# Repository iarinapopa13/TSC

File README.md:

# TSC
### Iarina-Ioana Popa, 332CA

# OpenBook eBook Reader – Hardware Overview
Acest proiect de eBook Reader utilizeaza microcontrollerul *ESP32-C6*, fiind proiectat pentru consum redus de energie, conectivitate avansata si adaptabilitate hardware.

## Diagrama Block

## Microcontroller – ESP32-C6
- *Arhitectura:* RISC-V 32-bit
- *Conectivitate:* WiFi 6, Bluetooth 5.0 LE
- *Interfete disponibile:* SPI, I2C, UART, PWM, GPIO
- *Eficienta energetica:* moduri deep sleep implementate

## Display E-Paper
- *Conectivitate:* Header de 20 pini dedicat
- *Protocol:* SPI + GPIO
 - Semnale principale: EPD_CS, EPD_DC, EPD_RST, EPD_BUSY, etc.
- *Beneficii:* zero consum in stare inactiva, vizibilitate superioara la lumina naturala

## Ceas Timp Real – DS3231SN
- *Caracteristici:* Precizie ridicata (±2 ppm)
- *Protocol:* I2C (partajat pe SDA/SCL)
- *Alimentare secundara:* Supercapacitor

## Senzor Ambiental – BME688
- *Masuratori:* Temperatura, Umiditate, Presiune atmosferica, VOCs
- *Interfata:* I2C
 - SDA: IO1
 - SCL: IO2
- *Alimentare:* 3.3V
- *Adresa I2C:* 0x76

## Sistem de Alimentare
### MAX17048 – Monitor Baterie
- *Rol:* Masurare capacitate baterie LiPo
- *Protocol:* I2C (IO1, IO2)
### MCP73831 – Controller Incarcare
- *Functionalitate:* Incarcare baterie LiPo (USB la 3.7V)
- *Capacitate:* ~500 mA
- *Indicator:* LED status incarcare
### XC6204 – Regulator LDO
- *Tensiune intrare:* 5V (USB)
- *Tensiune iesire:* 3.3V
- *Capacitate curent:* 200 mA
- *Eficienta energetica:* < 1 µA in standby

## Memorie si Stocare
### Card microSD
- *Protocol:* SPI (IO4–IO9)
- *Utilizare:* Stocare eBooks, setari
### Memorie Flash – W25Q512JV (64MB)
- *Protocol:* SPI (pini dedicati: IO20–IO23)
- *Utilizare:* Stocare firmware, fonturi, resurse

## Supervisor Tensiune & Resetare
- *Component:* BD52xx
- *Rol:* Monitorizare tensiune si resetare sigura
- *Pin control:* IO0

## Extensie I2C – Qwiic / Stemma QT
- *Conector:* 4 pini (3V3, GND, SDA, SCL)
- *Protocol:* I2C (IO1, IO2)
- *Ecosistem:* Compatibil cu module Adafruit / SparkFun

## Profil Consum Energetic
| Componenta             | Mod Activ       | Mod Standby    |
|------------------------|-----------------|----------------|
| ESP32-C6               | 80–150 mA       | <10 µA         |
| E-Paper                | 20–30 mA        | 0 µA           |
| BME688                 | 1.1 mA          | 0.15 µA        |
| RTC DS3231SN           | 200 µA          | 2 µA           |
| SD Card                | 20–100 mA       | 0.2 µA         |
| MAX17048               | 50 µA           | 1 µA           |
| NOR Flash              | 20 mA           | 5 µA           |

## Mapare Pini – ESP32-C6
| Functionalitate        | Pini GPIO            |
|------------------------|----------------------|
| Card SD (SPI)          | IO4, IO5, IO6, IO9   |
| Display E-Paper        | IO10–IO19            |
| I2C (RTC, Senzor)      | IO1 (SDA), IO2 (SCL) |
| Flash SPI extern       | IO20–IO23            |
| Buton Reset / Boot     | IO0                  |

## BOM (Bill Of Materials)
| Componenta | Link Cumpărare | Datasheet |
|------------|-----------------|-----------|
| Condensatoare Tantalum | [Buy](https://ro.mouser.com/ProductDetail/KYOCERA-AVX/TAJW107M010RNJ?qs=Wtp%252Bf%2FAeVqIH8v1VxV%252B1Rg%3D%3D) | [Datasheet](https://ro.mouser.com/datasheet/2/40/TAJ-3165264.pdf) |
| Rezistente R0402 | [Buy](https://store.comet.srl.ro/Search/?keywords=r0402#eyJpcHAiOiIyMCIsIm0iOiIiLCJrIjoicjA0MDIifQ%3D%3D) | [Datasheet](https://www.yageo.com/upload/media/product/products/datasheet/rchip/PYu-RC_Group_51_RoHS_L_12.pdf) |
| Condensatoare C0402 | [Buy](https://store.comet.srl.ro/CatalogueFarnell/Search/?keywords=c0402#eyJpcHAiOiIyMCIsImsiOiJjMDQwMiJ9) | [Datasheet](https://componentsearchengine.com/Datasheets/2/CC0402MRX5R5BB106.pdf) |
| 112A-TAAR-R03 | [Buy](https://store.comet.srl.ro/Catalogue/Product/43497/) | [Datasheet](https://www.snapeda.com/parts/112A-TAAR-R03/Attend/datasheet/) |
| SD0805S020S1R0 | [Buy](https://ro.mouser.com/ProductDetail/KYOCERA-AVX/SD0805S020S1R0?qs=jCA%252BPfw4LHbpkAoSnwrdjw%3D%3D) | [Datasheet](https://ro.mouser.com/datasheet/2/40/schottky-3165252.pdf) |
| MBR0530 | [Buy](https://ro.mouser.com/ProductDetail/onsemi-Fairchild/MBR0530?qs=VOMQJJE%252BBNniwJKcE3T43Q==) | [Datasheet](https://ro.mouser.com/datasheet/2/308/MBR0530_D-1810985.pdf) |
| CHG_LED | [Buy](https://ro.mouser.com/ProductDetail/Kingbright/KP-1608SURCK?qs=2JU0tDl2GZ3FuyEWfBV1%2Fg==) | [Datasheet](https://www.snapeda.com/parts/KP-1608SURCK/Kingbright/datasheet/) |
| PGB1010603MR | [Buy](https://www.digikey.com/en/products/detail/littelfuse-inc/PGB1010603MR/715755) | [Datasheet](https://www.littelfuse.com/assetdocs/pulseguard-esd-suppressors-pgb1-datasheet?assetguid=8a337998-d54d-466b-be4e-dc5bcd1f9321) |
| ESP32-C6-WROOM-1-N8 | [Buy](https://ro.mouser.com/ProductDetail/Espressif-Systems/ESP32-C6-WROOM-1-N8?qs=8Wlm6%252BaMh8ST02Gmwp74cw%3D%3D) | [Datasheet](https://ro.mouser.com/datasheet/2/891/Espressif_ESP32_C6_WROOM_1__Datasheet_V0_1_PRELIMI-3239987.pdf) |
| DS3231SN | [Buy](https://store.comet.srl.ro/Catalogue/Product/47690/) | [Datasheet](https://ro.mouser.com/datasheet/2/609/DS3231-3421123.pdf) |
| BME680 | [Buy](https://ro.mouser.com/ProductDetail/Bosch-Sensortec/BME688?qs=IS%252B4QmGtzzqQoVDscqwx3A%3D%3D) | [Datasheet](https://ro.mouser.com/datasheet/2/783/bst_bme688_fl000-2307034.pdf) |
| USBLC6-2SC6Y | [Buy](https://ro.mouser.com/ProductDetail/STMicroelectronics/USBLC6-2SC6Y?qs=gNDSiZmRJS%2FOgDexvXkdow%3D%3D) | [Datasheet](https://ro.mouser.com/datasheet/2/389/usblc6_2sc6y-1852505.pdf) 
| MAX17048 | [Buy](https://ro.mouser.com/ProductDetail/Analog-Devices-Maxim-Integrated/MAX17048G%2bT10?qs=D7PJwyCwLAoGnnn8jEPRBQ%3D%3D) | [Datasheet](https://ro.mouser.com/datasheet/2/609/MAX17048_MAX17049-3469099.pdf) |
| MCP73831 | [Buy](https://ro.mouser.com/ProductDetail/Microchip-Technology/MCP73831T-2ATI-OT?qs=yUQqVecv4qsZbioEUu%252B83g%3D%3D) | [Datasheet](https://ro.mouser.com/datasheet/2/268/MCP73831_Family_Data_Sheet_DS20001984H-3441711.pdf) |
| BD5229G-TR | [Buy](https://www.digikey.com/en/products/detail/rohm-semiconductor/BD5229G-TR/3663792) | [Datasheet](https://fscdn.rohm.com/en/products/databook/datasheet/ic/power/voltage_detector/bd52xxg-e.pdf) |
| W25Q512JVEIQ | [Buy](https://ro.mouser.com/ProductDetail/Winbond/W25Q512JVEIQ?qs=l7cgNqFNU1jw6svr3at6tA%3D%3D) | [Datasheet](https://ro.mouser.com/datasheet/2/949/Winbond_W25Q512JV_Datasheet-3240039.pdf) |
| XC6220A331MR-G | [Buy](https://ro.mouser.com/ProductDetail/Torex-Semiconductor/XC6220A331MR-G?qs=AsjdqWjXhJ8ZSWznL1J0gg%3D%3D) | [Datasheet](https://ro.mouser.com/datasheet/2/760/xc6220-3371556.pdf) |
| USB4110-GF-A | [Buy](https://ro.mouser.com/ProductDetail/GCT/USB4110-GF-A?qs=KUoIvG%2F9IlYiZvIXQjyJeA%3D%3D) | [Datasheet](https://ro.mouser.com/datasheet/2/837/GCT_USB4110_Product_Drawing___20k_cycles-3455479.pdf) |
| FH34SRJ | [Buy](https://ro.mouser.com/ProductDetail/Hirose-Connector/FH34SRJ-24S-0.5SH99?qs=vcbW%252B4%252BSTIpKBl5ap9J8Fw%3D%3D) | [Datasheet](https://ro.mouser.com/datasheet/2/185/FH34SRJ_24S_0_5SH_99__CL0580_1255_6_99_2DDrawing_0-1615044.pdf) |
| Si1308EDL-T1-GE3 | [Buy](https://www.digikey.com/en/products/detail/vishay-siliconix/SI1308EDL-T1-GE3/4876435) | [Datasheet](https://www.vishay.com/docs/63399/si1308edl.pdf) |
| PFMF.050.1 | [Buy](https://ro.mouser.com/ProductDetail/EPCOS-TDK/B72520T0350K062?qs=dEfas%2FXlABIszF52uu7vrg%3D%3D) | [Datasheet](https://www.tdk-electronics.tdk.com/inf/75/db/CTVS_14/Surge_protection_series.pdf) |
| DMG2305UX-7 | [Buy](https://www.digikey.com/en/products/detail/diodes-incorporated/DMG2305UX-7/4340666) | [Datasheet](https://www.diodes.com/assets/Datasheets/DMG2305UX.pdf) |
| SJ (Solder Jumpers) | [Buy](https://grabcad.com/library/solder-jumpers-1) | [Datasheet](https://grabcad.com/library/solder-jumpers-1) |
| Butoane | [Buy](https://industry.panasonic.com/global/en/products/control/switch/light-touch/number/evqpuj02k) | [Datasheet](https://industry.panasonic.com/global/en/downloads?tab=catalog&small_g_cd=203&part_no=EVQPUJ02K) |
| CPH3225A | [Buy](https://www.digikey.com/en/products/detail/seiko-instruments/CPH3225A/8692444) | [Datasheet](https://mm.digikey.com/Volume0/opasdata/d220001/medias/docus/6537/rev05-CPHCPM.pdf) |
| QWIIC_RIGHT_ANGLE | [Buy](https://ro.mouser.com/ProductDetail/SparkFun/PRT-14417?qs=wd5RIQLrsJhgdz%2FpmZ%2F3GQ==) | [Datasheet](https://ro.mouser.com/datasheet/2/813/Qwiic_Connector_Datasheet-1223982.pdf) |
| Bobine 744043680 | [Buy](https://ro.mouser.com/ProductDetail/Wurth-Elektronik/744043680?qs=PGXP4M47uW6VkZq%252BkzjrHA%3D%3D) | [Datasheet](https://www.we-online.com/components/products/datasheet/744043680.pdf) |

## Note aditionale
- Aproximativ 130 vias la PCB
- Placuta in format 3D prezinta o diferenta de cativa mm in zona de sud a acesteia
- TP-urile nu au putut fi plasate precum in schema initiala, pentru evitarea viasurilor acestea au fost plasate cat mai aproape fata de  componentele de care se legau in urma procesului de rutare
- Bobina a suferit modificari din cauza erorilor date de ERC
- U4 a suferit modificari la SMD hole
- Am deplasat putin la dreaota una dintre mufe pentru a alinia perfect USB-ul

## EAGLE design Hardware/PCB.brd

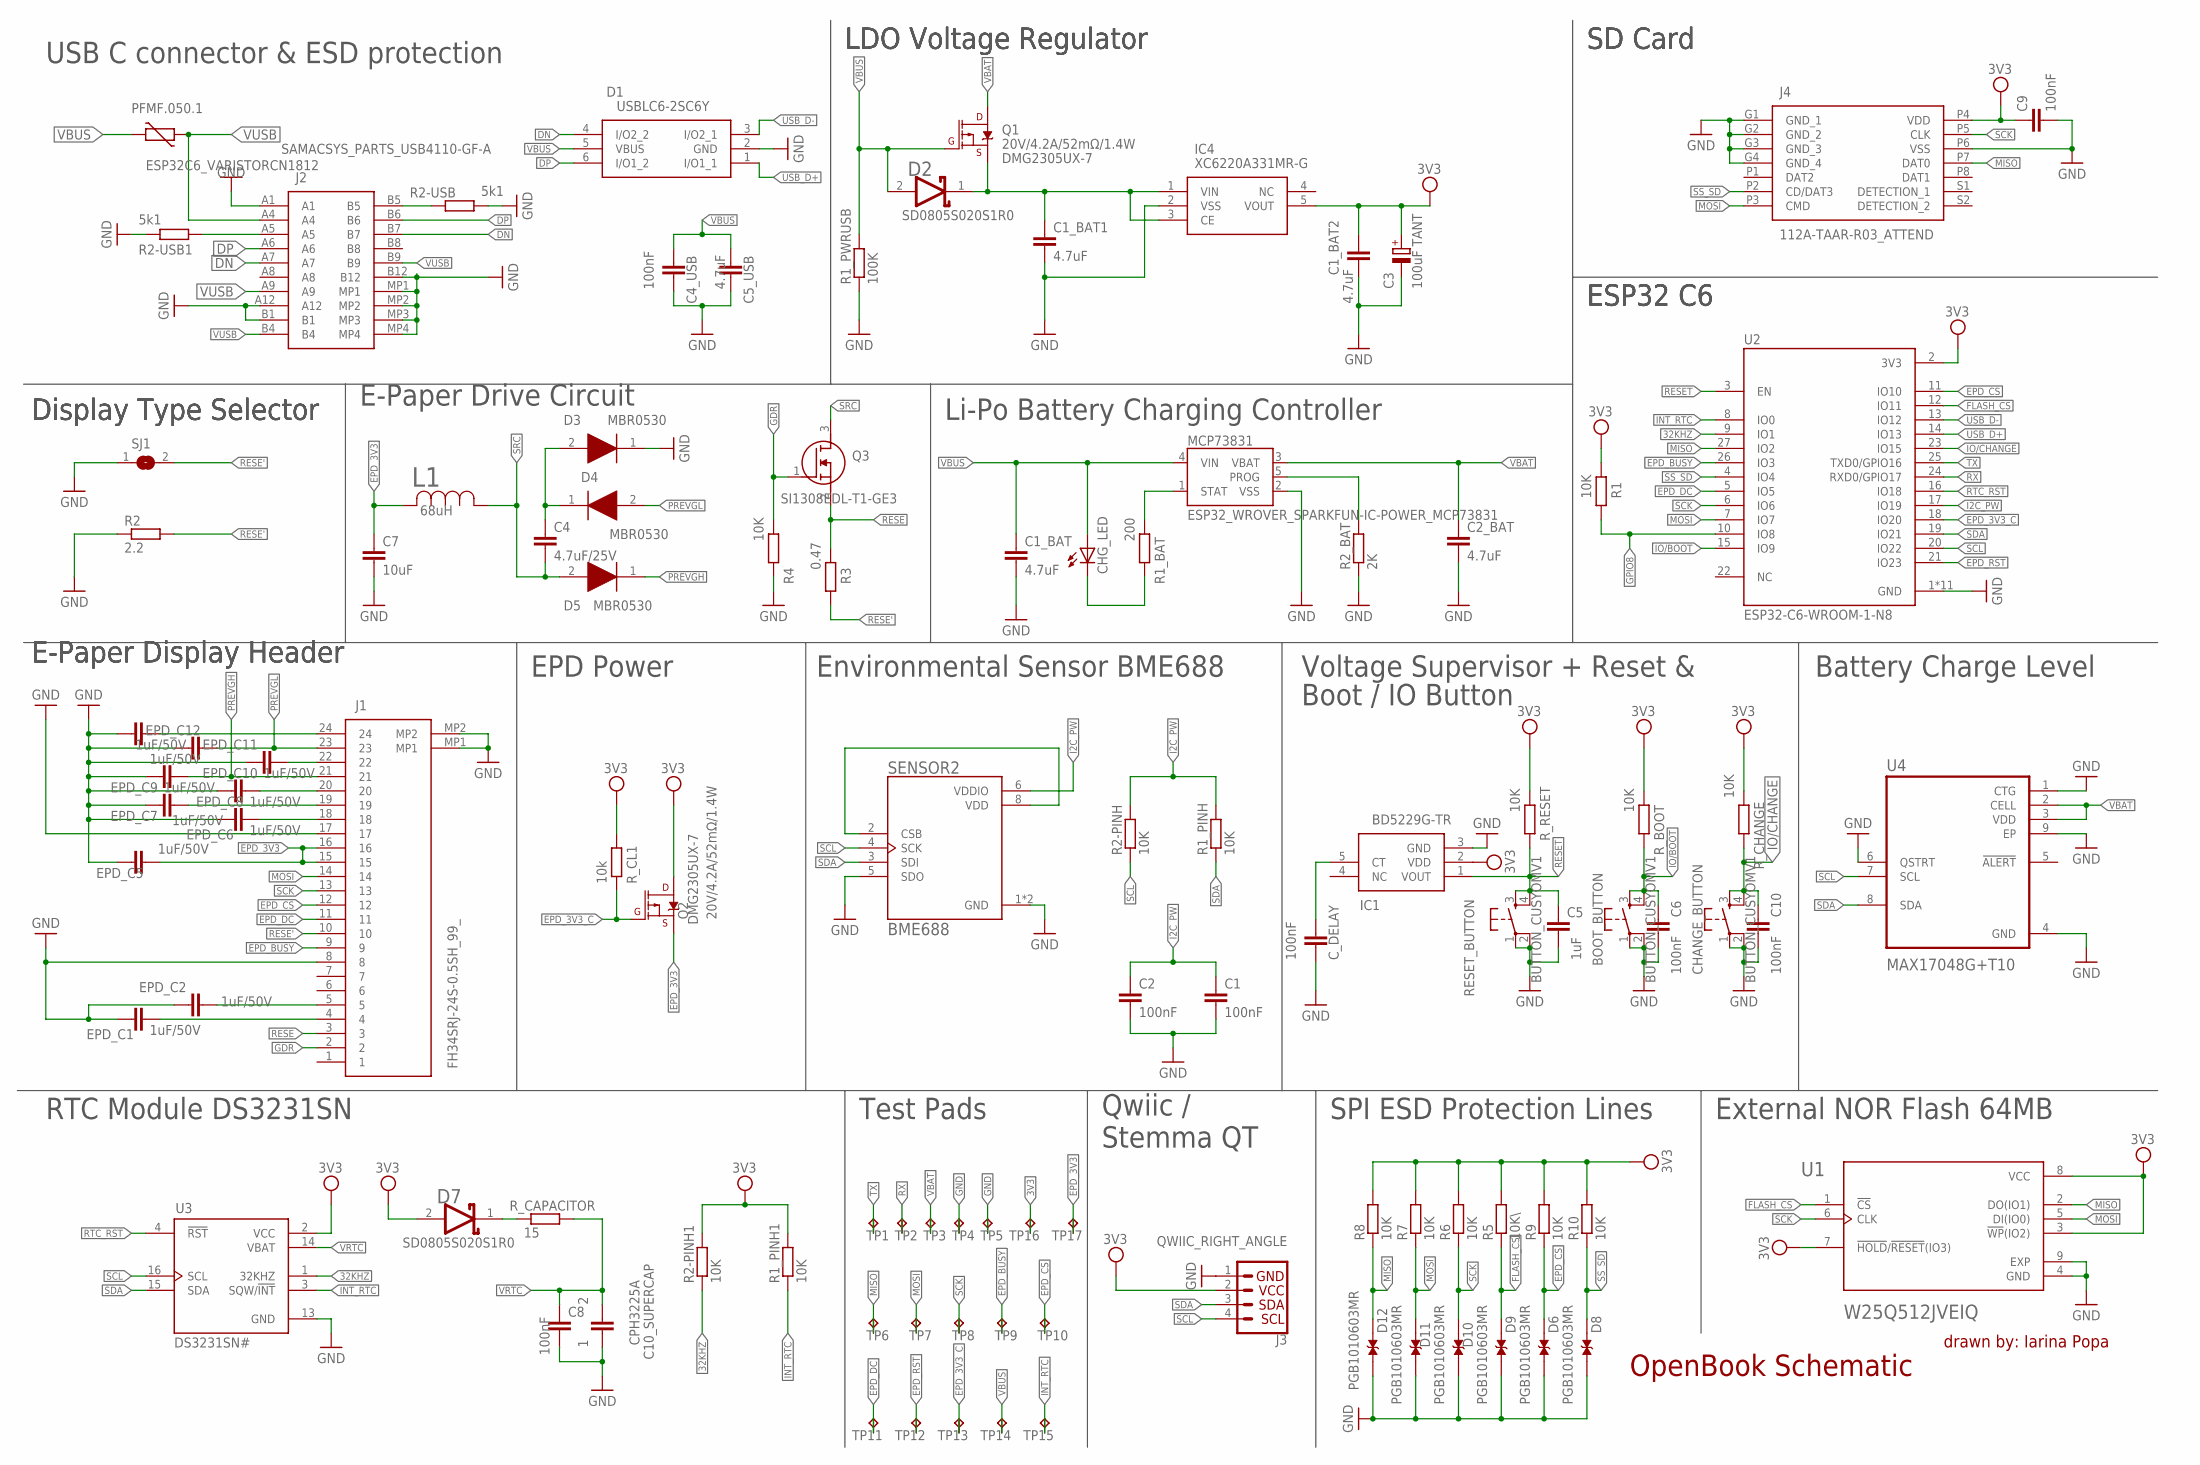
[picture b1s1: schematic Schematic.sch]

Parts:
BOOT_BUTTON: BUTTON_CUSYOMV1; MYBUTTON
C1, C2, C4_USB, C6, C8, C9, C10: 100nF; EAGLE-LTSPICE_C0402
C1_BAT, C1_BAT1, C1_BAT2, C2_BAT, C5_USB: 4.7uF; EAGLE-LTSPICE_C0402
C3: 100uF TANT; RCL_CT3528
C4: 4.7uF/25V; EAGLE-LTSPICE_C0402
C5: 1uF; EAGLE-LTSPICE_C0402
C7: 10uF; EAGLE-LTSPICE_C0402
C10_SUPERCAP: CPH3225A; EAGLE-LTSPICE_C0402
CHANGE_BUTTON: BUTTON_CUSYOMV1; MYBUTTON
CHG_LED: ADAFRUIT_LEDCHIP-LED0603; ADAFRUIT_CHIP-LED0603
C_DELAY: 100nF; EAGLE-LTSPICE_C0402
D1: USBLC6-2SC6Y; SOT95P280X145-6N
D2, D7: ESP32_WROVER_AVX---SD0805S020S1R0_AVX_SD0805S020S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; ESP32_WROVER_AVX---SD0805S020S1R0_AVX_SD0805S020S1R0_0
D3, D4, D5: MBR0530; SOD3716X135N
D6, D8, D9, D10, D11, D12: PGB1010603MR; DIOC1608X36N
EPD_C1, EPD_C2, EPD_C5, EPD_C6, EPD_C7, EPD_C8, EPD_C9, EPD_C10, EPD_C11, EPD_C12: 1uF/50V; EAGLE-LTSPICE_C0402
IC1: BD5229G-TR; SOT95P280X125-5N
IC4: XC6220A331MR-G; SOT95P280X120-5N
J1: FH34SRJ-24S-0.5SH_99_; FH34SRJ24S05SH99
J2: SAMACSYS_PARTS_USB4110-GF-A; SAMACSYS_PARTS_USB4110GFA
J3: QWIIC_RIGHT_ANGLE; JST04_1MM_RA
J4: 112A-TAAR-R03_ATTEND; 112ATAARR03ATTEND
L1: 68uH; IND_4828-WE-TPC_WRE
MCP73831: ESP32_WROVER_SPARKFUN-IC-POWER_MCP73831; ESP32_WROVER_SPARKFUN-IC-POWER_SOT23-5
PFMF.050.1: ESP32C6_VARISTORCN1812; ESP32C6_VARISTOR_CT/CN1812
Q1, Q2: 20V/4.2A/52mΩ/1.4W; ESP32_WROVER_SPARKFUN-DISCRETESEMI_SOT23-3
Q3: SI1308EDL-T1-GE3; SOT65P210X110-3N
R1, R1_PINH, R1_PINH1, R2-PINH, R2-PINH1, R4, R6, R7, R8, R9, R10: 10K; ESP32_WROVER_EAGLE-LTSPICE_R0402
R1_BAT: 200; ESP32_WROVER_EAGLE-LTSPICE_R0402
R1_PWRUSB: 100K; ESP32_WROVER_EAGLE-LTSPICE_R0402
R2: 2.2; ESP32_WROVER_EAGLE-LTSPICE_R0402
R2-USB, R2-USB1: 5k1; ESP32_WROVER_EAGLE-LTSPICE_R0402
R2_BAT: 2K; ESP32_WROVER_EAGLE-LTSPICE_R0402
R3: 0.47; ESP32_WROVER_EAGLE-LTSPICE_R0402
R5: 10K\; ESP32_WROVER_EAGLE-LTSPICE_R0402
RESET_BUTTON: BUTTON_CUSYOMV1; MYBUTTON
R_BOOT: 10K; ESP32_WROVER_EAGLE-LTSPICE_R0402
R_CAPACITOR: 15; ESP32_WROVER_EAGLE-LTSPICE_R0402
R_CHANGE: 10K; ESP32_WROVER_EAGLE-LTSPICE_R0402
R_CL1: 10k; ESP32_WROVER_EAGLE-LTSPICE_R0402
R_RESET: 10K; ESP32_WROVER_EAGLE-LTSPICE_R0402
SENSOR2: BME688; ESP32_WROVER_BME680_PSON80P300X300X100-8N
SJ1: SJ
TP1, TP2, TP3, TP4, TP5, TP6, TP7, TP8, TP9, TP10, TP11, TP12, TP13, TP14, TP15, TP16, TP17: TPTP20R; TP20R
U1: W25Q512JVEIQ; SON127P600X800X80-9N
U2: ESP32-C6-WROOM-1-N8; XCVR_ESP32-C6-WROOM-1-N8
U3: DS3231SN#; SOIC127P1032X265-16N
U4: MAX17048G+T10; SON50P200X200X80-9N

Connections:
3V3: C1_BAT2.1, C3.+, C9.1, D7.2 (ANODE), IC1.2 (VDD), IC4.5 (VOUT), J3.2, J4.P4 (VDD), Q2.3 (D), R1.2, R1_PINH1.2, R2-PINH1.2, R5.2, R6.2, R7.2, R8.2, R9.2, R10.2, R_BOOT.2, R_CHANGE.2, R_CL1.2, R_RESET.2, TP16.TP, U1.3 (!WP!(IO2)), U1.7 (!HOLD!/!RESET!(IO3)), U1.8 (VCC), U2.2 (3V3), U3.2 (VCC)
32KHZ: R2-PINH1.1, U2.9 (IO1), U3.1 (32KHZ)
DN: D1.4 (I/O2_2), J2.A7, J2.B7
DP: D1.6 (I/O1_2), J2.A6, J2.B6
EPD_3V3: C7.1, EPD_C5.2, J1.15, J1.16, L1.2, Q2.2 (S), TP17.TP
EPD_3V3_C: Q2.1 (G), R_CL1.1, TP13.TP, U2.18 (IO20)
EPD_BUSY: J1.9, TP9.TP, U2.26 (IO3)
EPD_CS: D6.2, J1.12, R9.1, TP10.TP, U2.11 (IO10)
EPD_DC: J1.11, TP11.TP, U2.5 (IO5)
EPD_RST: TP12.TP, U2.21 (IO23)
FLASH_CS: D9.2, R5.1, U1.1 (!CS), U2.12 (IO11)
GDR: J1.2, Q3.1 (G), R4.2
GND: BOOT_BUTTON.1, BOOT_BUTTON.2, C1.2, C1_BAT.2, C1_BAT1.2, C1_BAT2.2, C2.2, C2_BAT.2, C3.-, C4_USB.2, C5.2, C5_USB.2, C6.2, C7.2, C8.2, C9.2, C10.2, C10_SUPERCAP.2, CHANGE_BUTTON.1, CHANGE_BUTTON.2, C_DELAY.2, D1.2 (GND), D3.1 (K), D6.1, D8.1, D9.1, D10.1, D11.1, D12.1, EPD_C1.1, EPD_C2.1, EPD_C5.1, EPD_C6.1, EPD_C7.1, EPD_C8.1, EPD_C9.1, EPD_C10.1, EPD_C11.1, EPD_C12.1, IC1.3 (GND), IC4.2 (VSS), J1.8, J1.17, J1.MP1, J1.MP2, J2.A1, J2.A12, J2.B1, J2.B12, J2.MP1, J2.MP2, J2.MP3, J2.MP4, J3.1, J4.G1 (GND_1), J4.G2 (GND_2), J4.G3 (GND_3), J4.G4 (GND_4), J4.P6 (VSS), MCP73831.2 (VSS), R1_PWRUSB.1, R2.1, R2-USB.2, R2-USB1.1, R2_BAT.1, R4.1, RESET_BUTTON.1, RESET_BUTTON.2, SENSOR2.1 (GND), SENSOR2.5 (SDO), SENSOR2.7 (GND), SJ1.1, TP4.TP, TP5.TP, U1.4 (GND), U1.9 (EXP), U2.1 (GND), U2.28 (GND), U2.29_1 (GND), U2.29_2 (GND), U2.29_3 (GND), U2.29_4 (GND), U2.29_5 (GND), U2.29_6 (GND), U2.29_7 (GND), U2.29_8 (GND), U2.29_9 (GND), U3.13 (GND), U4.1 (CTG), U4.4 (GND), U4.6 (QSTRT), U4.9 (EP)
GPIO8: R1.1, U2.10 (IO8)
I2C_PW: C1.1, C2.1, R1_PINH.2, R2-PINH.2, SENSOR2.6 (VDDIO), U2.17 (IO19)
INT_RTC: R1_PINH1.1, TP15.TP, U2.8 (IO0), U3.3 (SQW/!INT)
IO/BOOT: BOOT_BUTTON.3, BOOT_BUTTON.4, C6.1, R_BOOT.1, U2.15 (IO9)
IO/CHANGE: C10.1, CHANGE_BUTTON.3, CHANGE_BUTTON.4, R_CHANGE.1, U2.23 (IO15)
MISO: D12.2, J4.P7 (DAT0), R8.1, TP6.TP, U1.2 (DO(IO1)), U2.27 (IO2)
MOSI: D11.2, J1.14, J4.P3 (CMD), R7.1, TP7.TP, U1.5 (DI(IO0)), U2.7 (IO7)
unnamed: J2.A5, R2-USB1.2
unnamed: J2.B5, R2-USB.1
unnamed: MCP73831.1 (STAT), R1_BAT.2
unnamed: CHG_LED.C, R1_BAT.1
unnamed: C1_BAT1.1, D2.1 (CATHODE), IC4.1 (VIN), IC4.3 (CE), Q1.2 (S)
unnamed: C4.1, D3.2 (A), D4.1 (K)
unnamed: MCP73831.5 (PROG), R2_BAT.2
unnamed: EPD_C1.2, J1.4
unnamed: EPD_C10.2, J1.22
unnamed: C_DELAY.1, IC1.5 (CT)
unnamed: EPD_C12.2, J1.24
unnamed: D7.1 (CATHODE), R_CAPACITOR.1
unnamed: EPD_C7.2, J1.19
unnamed: EPD_C8.2, J1.20
unnamed: EPD_C6.2, J1.18
unnamed: SENSOR2.2 (CSB), SENSOR2.8 (VDD)
unnamed: EPD_C2.2, J1.5
PREVGH: D5.1 (K), EPD_C9.2, J1.21
PREVGL: D4.2 (A), EPD_C11.2, J1.23
RESE: J1.3, Q3.2 (S), R3.2
RESE': J1.10, R2.2, R3.1, SJ1.2
RESET: C5.1, IC1.1 (VOUT), RESET_BUTTON.3, RESET_BUTTON.4, R_RESET.1, U2.3 (EN)
RTC_RST: U2.16 (IO18), U3.4 (!RST)
RX: TP2.TP, U2.24 (RXD0/GPIO17)
SCK: D10.2, J1.13, J4.P5 (CLK), R6.1, TP8.TP, U1.6 (CLK), U2.6 (IO6)
SCL: J3.4, R2-PINH.1, SENSOR2.4 (SCK), U2.20 (IO22), U3.16 (SCL), U4.7 (SCL)
SDA: J3.3, R1_PINH.1, SENSOR2.3 (SDI), U2.19 (IO21), U3.15 (SDA), U4.8 (SDA)
SRC: C4.2, D5.2 (A), L1.1, Q3.3 (D)
SS_SD: D8.2, J4.P2 (CD/DAT3), R10.1, U2.4 (IO4)
TX: TP1.TP, U2.25 (TXD0/GPIO16)
USB_D+: D1.1 (I/O1_1), U2.14 (IO13)
USB_D-: D1.3 (I/O2_1), U2.13 (IO12)
VBAT: C2_BAT.1, MCP73831.3 (VBAT), Q1.3 (D), TP3.TP, U4.2 (CELL), U4.3 (VDD)
VBUS: C1_BAT.1, C4_USB.1, C5_USB.1, CHG_LED.A, D1.5 (VBUS), D2.2 (ANODE), MCP73831.4 (VIN), PFMF.050.1.2, Q1.1 (G), R1_PWRUSB.2, TP14.TP
VRTC: C8.1, C10_SUPERCAP.1, R_CAPACITOR.2, U3.14 (VBAT)
VUSB: J2.A4, J2.A9, J2.B4, J2.B9, PFMF.050.1.1

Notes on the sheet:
USB C connector & ESD protection
LDO Voltage Regulator
SD Card
ESP32 C6
Li-Po Battery Charging Controller
E-Paper Drive Circuit
Display Type Selector
E-Paper Display Header
EPD Power
Environmental Sensor BME688
Boot / IO Button
Voltage Supervisor + Reset &
Battery Charge Level
RTC Module DS3231SN
Test Pads
Qwiic / Stemma QT
SPI ESD Protection Lines
External NOR Flash 64MB
OpenBook Schematic
drawn by: Iarina Popa

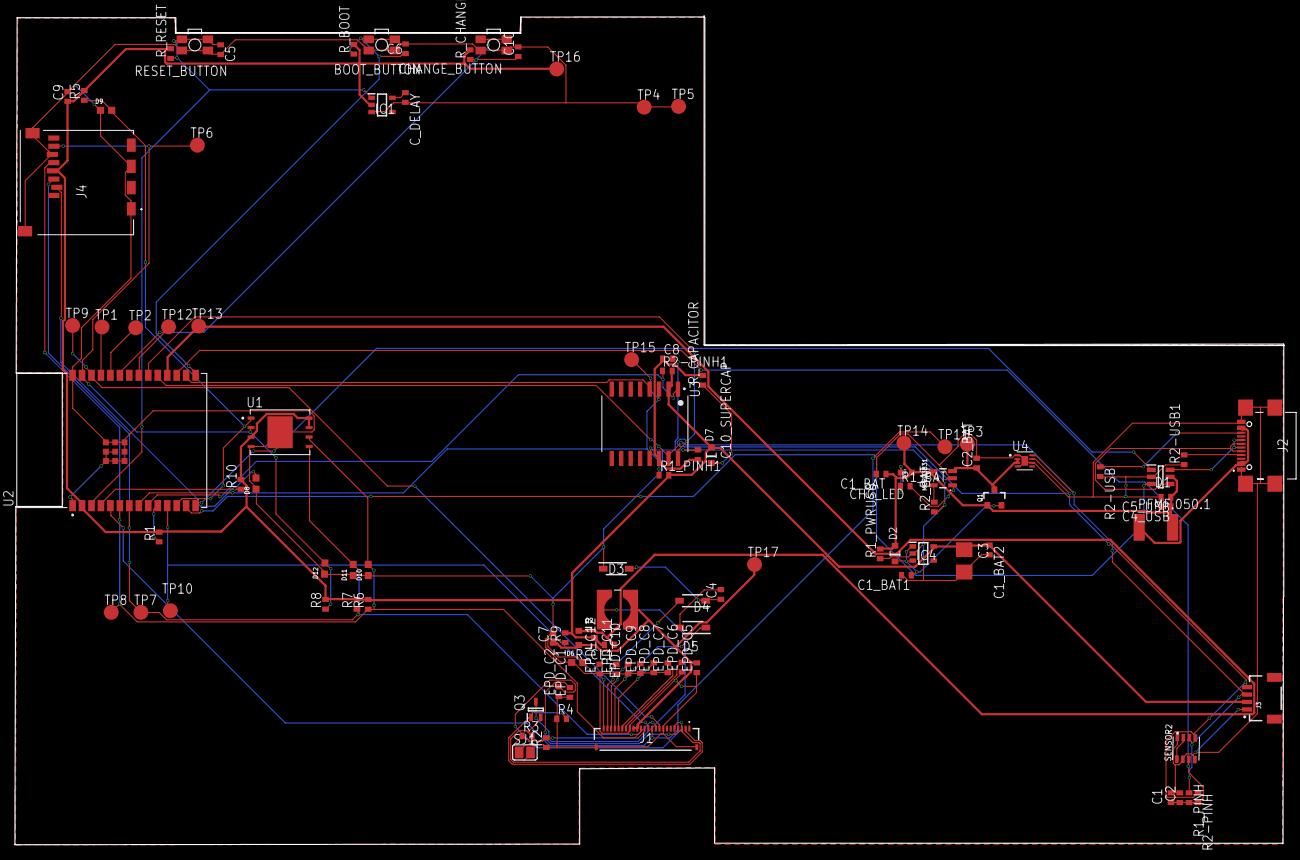
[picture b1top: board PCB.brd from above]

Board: 2 copper layers, 170.3 x 111.1 mm, 103 parts (0 on the bottom side), 56 nets.

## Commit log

2025-04-05 Create LICENSE

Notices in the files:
parts and their libraries:
COPYRIGHT: Copyright (C) 2024 Ultra Librarian. All rights reserved.
